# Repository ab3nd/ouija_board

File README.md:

# Ouija Board
Hardware and software plans for a ouija board that is controlled by a computer as an IO device. 

Now that this is public, I thought I ought to write up a bit more of a description of what we had hoped to do, what ended up making it into the puzzle, lessons learned, and so forth. 

The initial idea of the puzzle was that players would play some sort of word game with Spirits From Beyond. The players would enter letters by sliding the Ouija board planchette around the board, and the machinery under the board would answer back. Since the easy way to drive the planchette from under the board was a magnet, we looked at a couple of different approaches for figuring out where the magnet was on the board. 

One approach was to cover the underside of the board with magnetic field visualization film, and then look at it with a camera. This has two main drawbacks, one of them being that field visualization film is expensive, and the other is that the camera has to have enough space to see the underside of the board, an unobstructed view (so the machinery has to move out of the way), and good light. This is annoying set of constraints to deal with. 

Magnets can also be sensed with Hall Effect sensors. One idea was to put a grid of sensors under the board, and interpolate the location of the planchette from the readings of multiple sensors, another option was to just have a sensor under each letter. Having a sensor under each letter means you can lose the planchetette if it's moved to some place that isn't a letter. Having a grid of sensors of sufficient resolution to detect the planchette at any location would mean we blew the budget building a PCB the size of a Ouija board, and then yours truly went nuts hand-soldering a bunch of SOT-23 parts (or I guess we contaminate someone's oven stenciling and reflowing them). So we didn't do that. 

The final approach was that the head of the machine that moves the planchette also had a ring of sensors. When it was moving the planchette, it would raise a magnet to engage the planchette, and then move to drag the planchette around. When it was sensing user input, it would lower the magnet, so it was only sensing the planchette magnet, and then move to keep the field over the sensor ring balanced. Since it was counting steps that it made to keep the magnet centered, the system would know what letter the sensor ring was under. This approach kept the sensor PCB small, reduced the number of parts needed, and could track the planchette anywhere. 

But wait, you say. When the puzzle was in operation, the players would say the word they wanted to input, and the system would then spell it and do some wiggling between yes and no. There was no actual use of the planchette as an input device!

Using the planchette as an input device had a number of problems. One was that the system could lose the planchette due to users moving it too fast, or picking it up and putting it back down somewhere else. We could have fixed that by having the system sweep the board, but that leads into the second problem, which is that there was no feedback. If the user spelled "obliges", but were closer to the 'h' than the 'i' and the system saw "oblhges", the user wouldn't have a way to see that it hadn't picked up their input properly. If it lost the planchette and was doing a sweep to find it again, the user would have no idea what was going on, and the system would be ignoring their input. 

Also, when people are properly using a Ouija board to communicate with Spirits from Beyond, they say their questions, and the spirits answer by pushing the planchette around (or it's the ideomotor effect, or Joe (that jerk) always tries to make it spell "dongs"). Since we didn't have a good way to contact players of the Game who have passed Beyond the Veil, we used baby monitors in the room with each Ouija board, and a person listening to the baby monitor. The person was SSHed into the Raspberry PI that was running each board, and used a little script to drive the planchette around. That was why the boards sometimes spelled out things like "NATO", to try to get people to spell things out with the NATO phonetic alphabet, in cases where the word they said was unclear. So while the players were speaking to Spirits from Beyond, the spirits still had their mortal shells, and were Beyond the room divider, rather than the Veil of Death.

### Actual Implementation Information

The gantry that moved the planchette was a cheapo CNC device skellington from AliExpress, which uses an Arduino and a couple of stepper motor drivers. Two of the motors drive one axis, the other axis only has one motor. They had the somewhat weird design decision that the Arduino is powered over USB, while the stepper drivers and motors have their own, independent power supply. This makes some sense, since it means that A) the Arduino doesn't need to be protected from noise from the stepper motors, and B) the parts that would normally do A are not needed, so the whole thing is cheaper for the Chinese factory it came from. 

The Arduino was controlled over a serial-over-USB link from a Raspberry Pi running stock Raspbian. A little python script presented a user interface for a person connected to the Pi via SSH, and took care of stuff like Mastermind solving, because humans are made of fallible meat, and so cannot be trusted to do Mastermind in their heads at 2AM. 

The Python for the UI and Mastermind solving is in user_console.py and mastermind.py. The control code for the Arduino is in ouija_control.ino. They communicate using a pretty simple text-based protocol. The incomplete code for following the planchette is in sensor_track.ino. It results in some very jerky movement, and it would probably be better to do some form of vector representation of the magnet displacement and a PID loop to drive that to zero when the magnet is well-centered, as well as velocity control to have it operate smoothly, but that's Left As An Exercise For The Reader. 

### Hardware Notes

The sensors we used are AH49ENTR Hall effect sensors, SOT23-3 case size. We didn't do a lot of work to characterize sensors or anything, these are just what Ross happened to have on hand. He also had the 74hc4051 8ch analog demux that was used to communicate with the sensors. The sensor ring had 8 sensors, and the mux/demux has 8 channels, addressed with three address lines, so the total pin count going into the Arduino just fit what we had available after handling the stepper controllers, limit switches, and the servo to raise/lower the magnet. Of course, none of this got used in the final version except the limit switches. 

The limit switches allow the system to drive the planchette dragging magnet to a corner, and then count steps when moving the planchette to know where it is on the board. There are only one set of limit switches, the other end of each axis' travel is handled in software, by knowing how many steps it is to the other side of the board, and not taking steps that would move the head beyond that limit. 

The sense ring PCB design is in the sense_pcb folder in this repo. It was designed in Kicad, so between that, Python, etc. pretty much the whole thing except the servo control modules and the board they are on is open source. If you get the PCBs made, OSHPark will do a slightly more expensive job of it, while DirtyPCBs will do it cheaper and far slower. I've used both, they're both good. 

The CNC gantries that moved the magnet under the board were cut down from their orignal size. Aluminum is soft. If you want to cut it, it will smear like butter into hacksaws and abrasive wheels. The tool to use is just normal wood cutting implements, like miter saws and whatnot. 

Raspbian is pretty rough around the edges, I rant about it with a lot of swearing here:

http://gizmosmith.com/2019/08/28/raspbian-still-bad/

http://gizmosmith.com/2019/08/11/the-year-of-linux-on-the-desktop-is-ha-get-fucked/

### Measurements of Ouija board

Letters - 30mm tall by 14mm (I) - 38mm (W)

"NO" - 20mm tall by 35mm wide

"YES" - 20mm tall by 45mm wide

"GOOD BYE" - 20mm by 170mm wide

Closest approach to board edge - 25mm (bottom of "GOOD BYE")

Board thickness - 3.5mm

So the maximum radius of the sense ring is 25mm + 20mm/2 = 35mm, to be able to have the center of the actuated planchette window over the centerline of the letters closest to the edge of the board. 

The minimum diameter of the sense ring would be set by the size of the letters, and appears to be around 30-35mm, so a radius of 15-17mm. 

So the radius should be at minimum 15-17mm, and at maxium 35mm, bigger is easier to build (more PCB space), but 17mm can probably fit a ring. 

Active area is a box bounded by "YES/NO" at the top, "GOOD BYE" at the bottom, and the edges of the alphabet at the sides.
These measurements are from Sarah's board, which is the 1972 Parker/Berverly board, whereas those above are from my board, a 1960s Parker/Salem board. 

Width (outside of N to outside of Z) - 360mm
Height (top of YES/NO to bottom of GOODBYE) - 230mm

Board 295mm x 445mm (Conveniently, just inside the cutting area of my laser cutter)

These measurements are from my Ouija board, which is the older model. 

Width (outside of N to outside of Z) - 375mm
Height (top of YES/NO to bottom of GOODBYE) - 235mm

Board 295mm by 446mm

So the board size is essentially exactly the same, but the printing is a little different. The same size of plotter can work with either board, and the differences in text location can be handled by calibration. 

### Some CNC Devices to Use

A4 paper size is 210 mm × 297 mm (8.27 in × 11.7 in), so the plotters with an A4-sized area are a little too small for a traditional Ouija board. 
A3 paper is 297 mm × 420 mm (11.69 in × 16.54 in), so an A3 plotter would work. 

https://www.aliexpress.com/item/DIY-XY-Plotter-drawbot-pen-drawing-robot-machine-lettering-corexy-A4-A3-engraving-area-frame-plotter/32952725307.html?spm=2114.search0204.3.16.11db7b78WONW3n&ws_ab_test=searchweb0_0,searchweb201602_6_10065_10130_10068_10890_10547_319_10546_317_10548_10545_10696_453_10084_454_10083_10618_10307_537_536_10902_10059_10884_10887_321_322_10103,searchweb201603_16,ppcSwitch_0&algo_expid=b5854729-7ad1-4867-a162-900024d3b36f-2&algo_pvid=b5854729-7ad1-4867-a162-900024d3b36f

https://www.aliexpress.com/item/50-X-65cm-Laser-Engraving-Machine-Wood-Router-CNC-DIY-Laser-Engraver-Machine-For-Desktop-Cutting/32970303676.html?spm=2114.search0204.3.96.5e8f46b0ur8a8C&ws_ab_test=searchweb0_0,searchweb201602_6_10065_10130_10068_10890_10547_319_10546_317_10548_10545_10696_453_10084_454_10083_10618_10307_537_536_10902_10059_10884_10887_321_322_10103,searchweb201603_16,ppcSwitch_0&algo_expid=b95455ae-6d0d-4979-8a5e-edf8464dbc0f-14&algo_pvid=b95455ae-6d0d-4979-8a5e-edf8464dbc0f

Second one is huge, could be cut down to fit under board. Very tall, though. 

### Magnet Grip

We replaced the planchette window/pointer with a cut piece of acrylic with a neodymium magnet in it, 5mm is about the max diameter for the magnet to still have it look good.

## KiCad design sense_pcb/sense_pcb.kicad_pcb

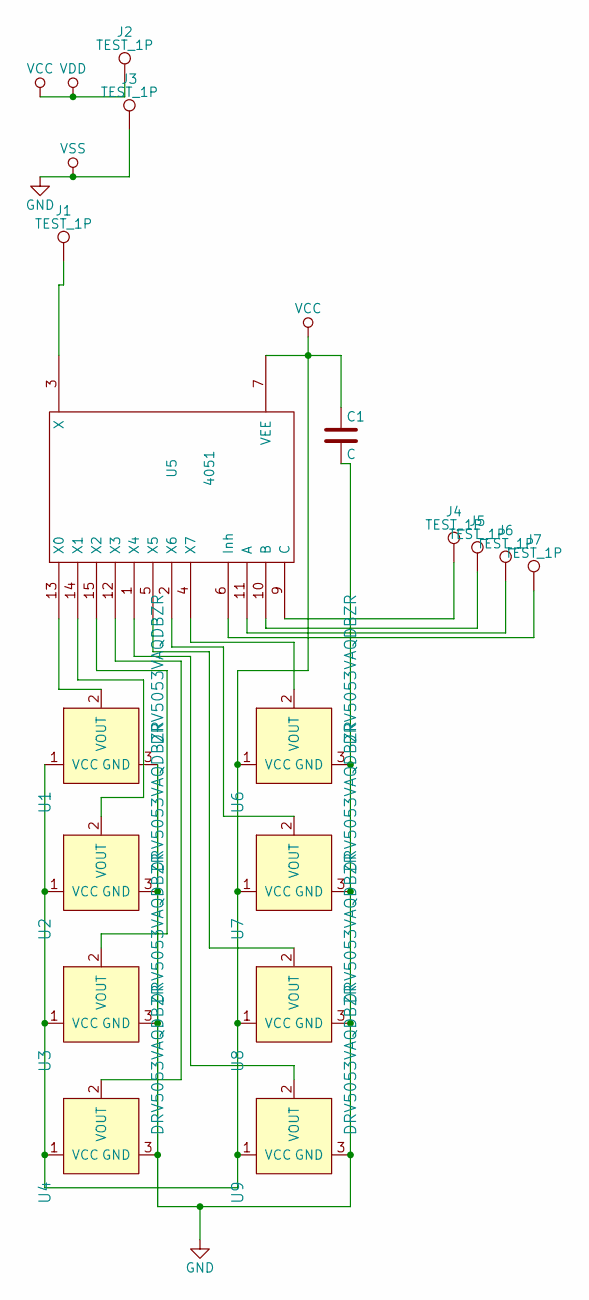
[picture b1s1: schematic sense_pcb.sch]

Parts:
C1: C; C_1206_HandSoldering
J1, J2, J3, J4, J5, J6, J7: TEST_1P; Measurement_Point_Round-SMD-Pad_Small
U1, U2, U3, U4, U6, U7, U8, U9: DRV5053VAQDBZR; SOT-23-3; MPN DRV5053VAQDBZR; Digi-Key_PN 296-38460-1-ND
U5: 4051; SO-16-N

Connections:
GND: C1.2, J3.1, U1.3 (GND), U2.3 (GND), U3.3 (GND), U4.3 (GND), U5.8 (VSS), U6.3 (GND), U7.3 (GND), U8.3 (GND), U9.3 (GND)
unnamed: J1.1, U5.3 (X)
unnamed: J4.1, U5.9 (C)
unnamed: J5.1, U5.10 (B)
unnamed: J6.1, U5.11 (A)
unnamed: J7.1, U5.6 (Inh)
unnamed: U1.2 (VOUT), U5.13 (X0)
unnamed: U2.2 (VOUT), U5.14 (X1)
unnamed: U3.2 (VOUT), U5.15 (X2)
unnamed: U4.2 (VOUT), U5.12 (X3)
unnamed: U5.1 (X4), U9.2 (VOUT)
unnamed: U5.2 (X6), U7.2 (VOUT)
unnamed: U5.4 (X7), U6.2 (VOUT)
unnamed: U5.5 (X5), U8.2 (VOUT)
VCC: C1.1, J2.1, U1.1 (VCC), U2.1 (VCC), U3.1 (VCC), U4.1 (VCC), U5.7 (VEE), U5.16 (VDD), U6.1 (VCC), U7.1 (VCC), U8.1 (VCC), U9.1 (VCC)

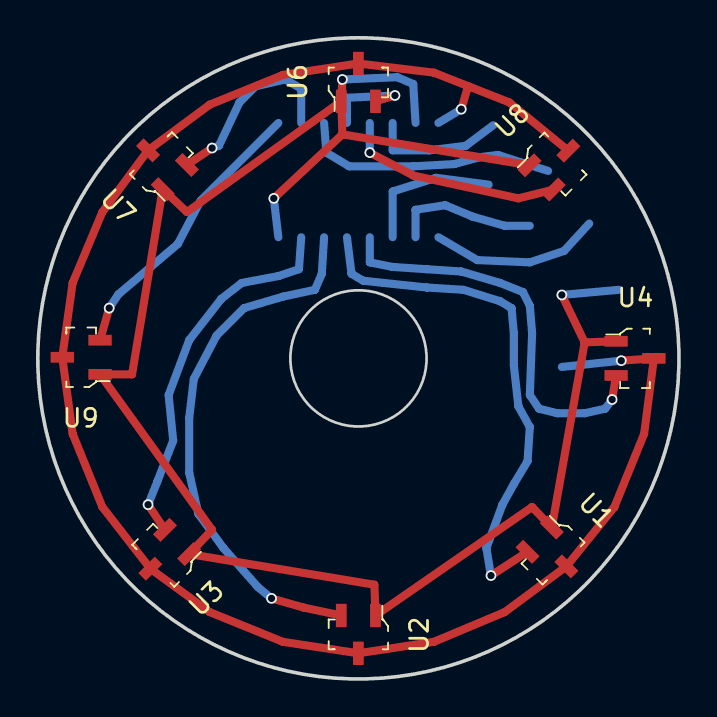
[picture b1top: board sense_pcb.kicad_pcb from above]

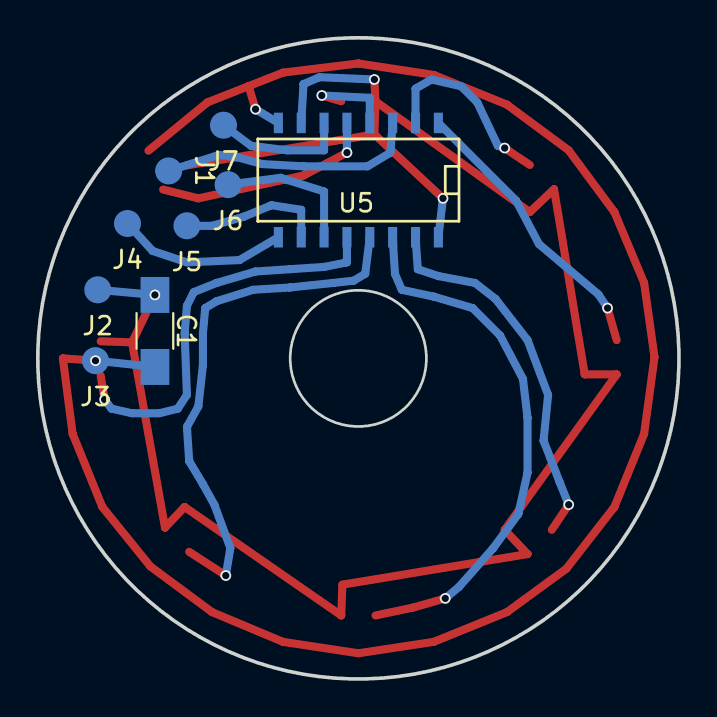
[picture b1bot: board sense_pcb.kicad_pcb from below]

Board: 2 copper layers, 35.6 x 35.6 mm, 17 parts (9 on the bottom side), 15 nets.

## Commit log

2019-03-02 adds datasheets
2019-03-02 adds sense pcb schematic
2019-03-02 adds component footprints
2019-03-02 adds netlist and pcb
2019-03-02 adds measurements
2019-03-02 adds graphics
2019-03-02 adds 35mm layout for parts
2019-03-02 IC layout done
2019-03-02 much smaller pads
2019-03-11 updated notes on ring size, new module
2019-03-11 removed 2/3 of the sensors from the schematic to shrink it
2019-03-11 went over to Kicad 5.0, seems legit so far
2019-03-11 layout with 8 sensors, no routing yet
2019-03-11 routing complete
2019-03-11 adds v1 manufacturing files as sent to dirtypcbs.com
2019-03-14 Update README.md
    Additional dimensional notes
2019-03-19 adds draft window cutout
2019-03-30 basic control of the steppers
2019-04-02 adds draft hardware for mounting magnet, servo, sense pcb
2019-04-28 adds sensor test
2019-04-28 sensor test program works, there is a bug in the PCB (Vee -> gnd, not v+)
2019-05-02 new version pcb holder
2019-05-02 Magnet holder in seperate file
2019-05-05 angle and speed calculations
2019-05-05 redesign of pcb holder
2019-05-05 removed some of the coordinate combination
2019-05-12 moving testing to real hardware
2019-05-13 updated pcb from laptop
2019-05-19 new limit test, servo for magnet
2019-05-22 move commands move the system, home command sends it home
2019-05-23 adds coords of the letters, in steps offset from 0,0
2019-05-24 adds wiggling for double letters, commands for yes/no
2019-07-29 adds first cut at sensor tracking
2019-08-03 basic letter reporting, needs state machine design
2019-08-03 following, sends characters, needs de-duplication on the other end
2019-08-03 better state handling, yes detection
2019-08-04 tuning, found some non-crap constants for following the planchette
2019-08-04 more tuning
2019-08-04 multiple loops of execution worked, servo still has issues
2019-08-08 adds mastermind checking
2019-08-10 adds files for switch mounts
2019-08-10 adds mastermind checker
2019-08-13 adds test to mastermind
2019-08-13 adds basic magnet holder
2019-08-17 adds info command
2019-08-17 switched sense of answer command
2019-11-09 Update README.md
    Expanded writeup for release
2019-11-09 Update README.md
    Line breaks!
2019-11-09 Update README.md
    More hardware info
